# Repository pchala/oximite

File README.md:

# oximite

**oximite** is an asynchronous Rust firmware suite for the Pimoroni Pico Plus 2 W (RP2350B). It retrofits domestic espresso machines (such as the Gaggia Classic) with digital temperature control (with flow feed-forward), unified pressure/flow pump profiling, a lightweight offline web UI on port 80, and a native desktop companion application (`control/`) over TCP port 8080.

Special thanks to [Pimoroni](https://pimoroni.com) for providing hardware.

Support development by [leaving a tip on Ko-fi](https://ko-fi.com/J5E121FXSB).

## Workspace layout

- `proto/`: Shared `no_std` domain models and Port 80/8080 wire codecs (`oximite-proto`).
- `firmware/`: RP2350B firmware and lightweight offline HTML dashboard.
- `host-tests/`: Host unit, property/fuzz, and closed-loop simulation test suite.
- `control/`: Native Rust desktop application (`oximite-control`) for live graphing, PID tuning, profile editing, and bench sweeps.

## Getting started

- Repository layout, build, and test commands: [AGENTS.md](AGENTS.md).
- Documentation: [docs/](docs/). Start at [Requirements](docs/requirements.md).
- First-time setup: [Operations](docs/operations.md).

## Disclaimer

All hardware designs, code, and documentation are provided "AS IS", without warranty of any kind.
You are solely responsible for electrical and thermal safety when working with AC mains voltages and pressurized steam boilers.

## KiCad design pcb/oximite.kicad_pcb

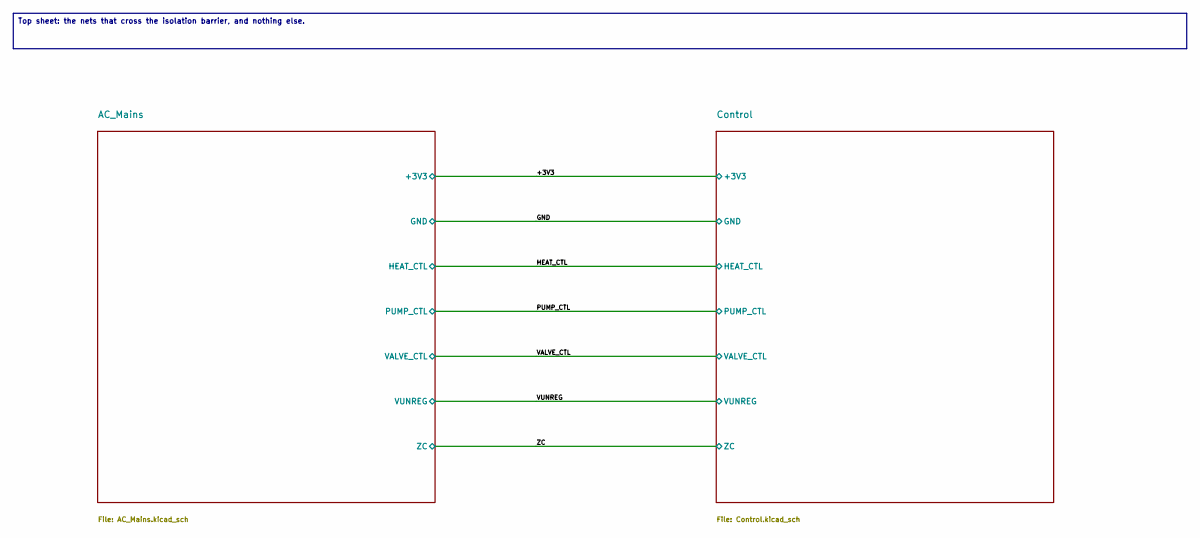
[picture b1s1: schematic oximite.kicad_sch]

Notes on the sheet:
Top sheet: the nets that cross the isolation barrier, and nothing else.

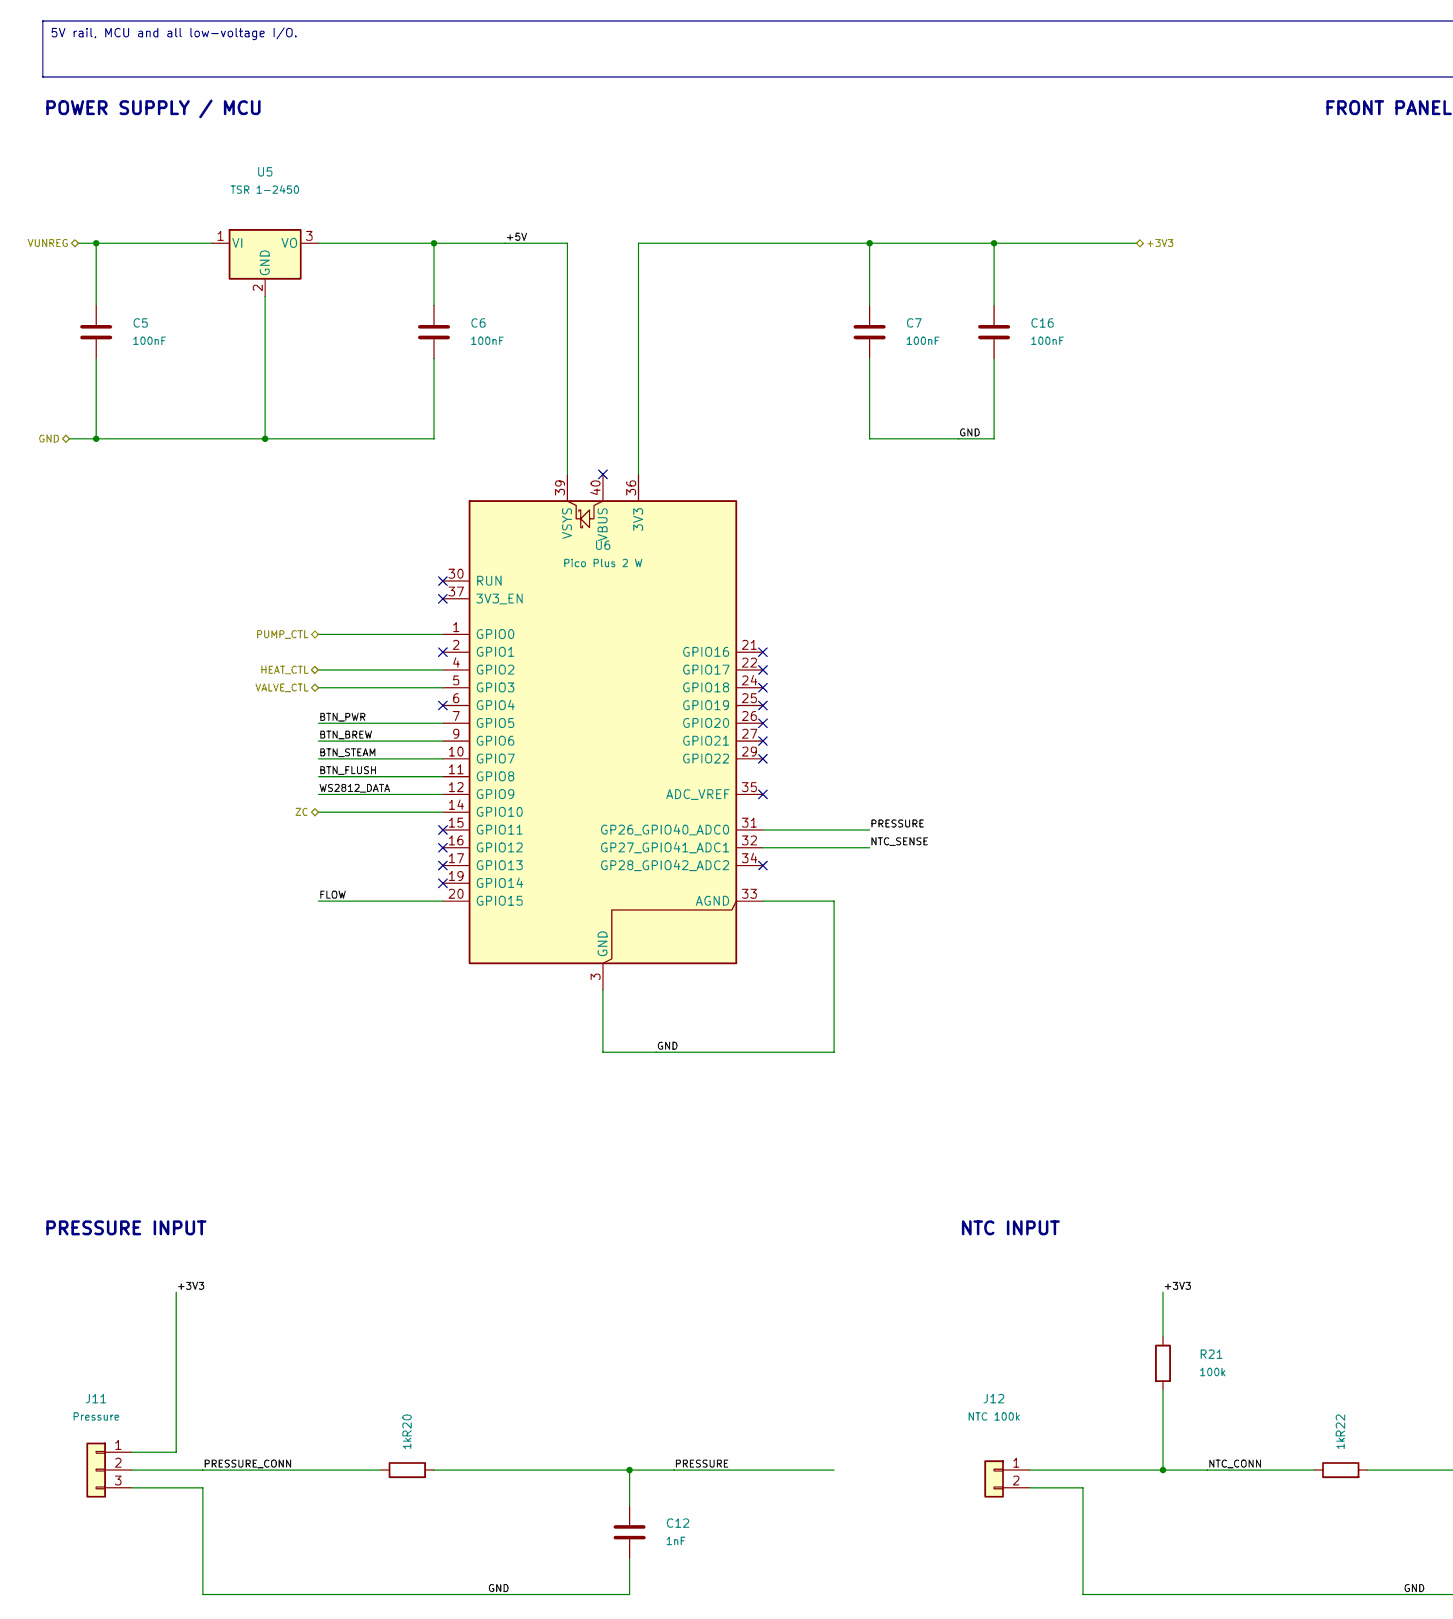
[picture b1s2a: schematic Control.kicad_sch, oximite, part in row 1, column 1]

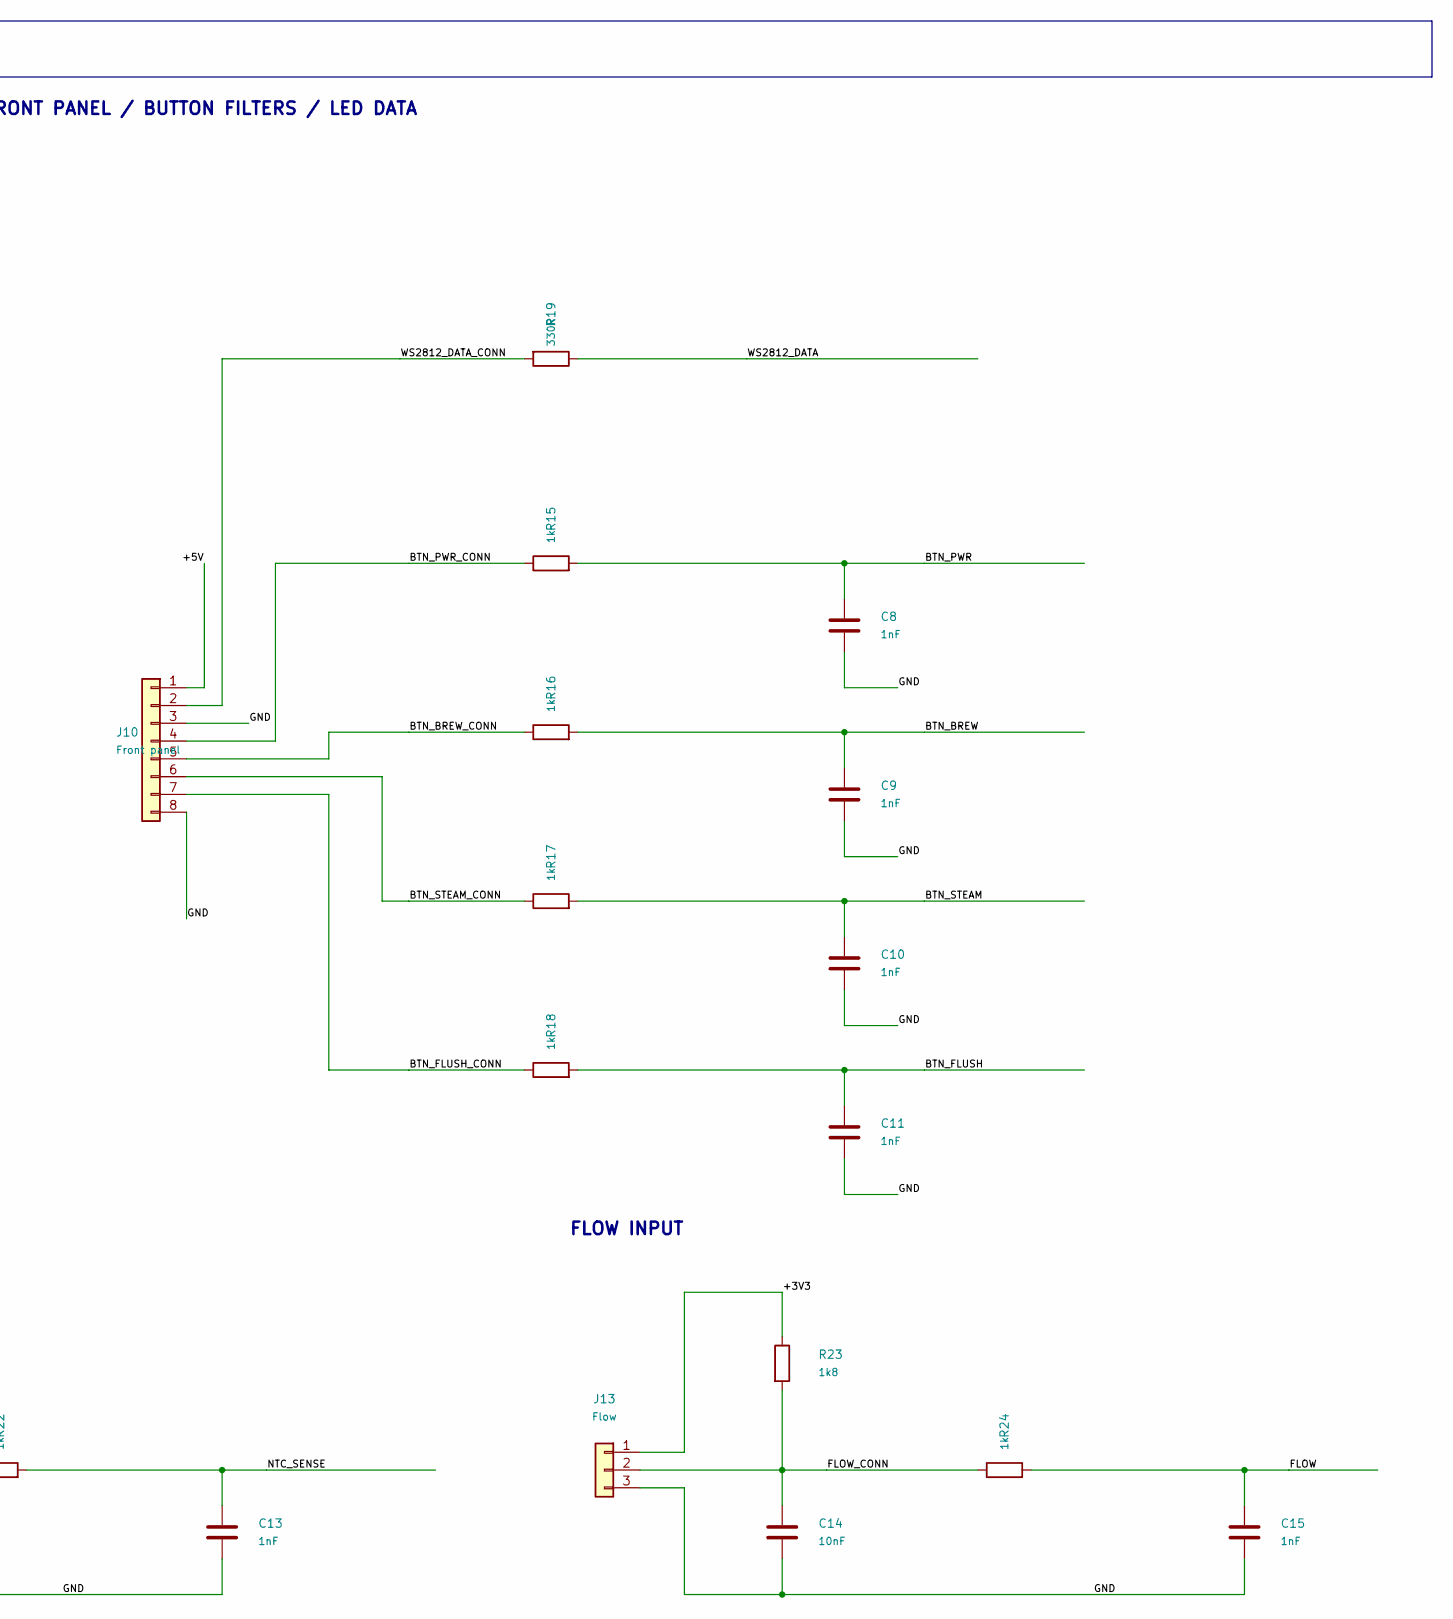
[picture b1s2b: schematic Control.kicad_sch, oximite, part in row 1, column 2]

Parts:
C5, C6, C7, C16: 100nF; C_0603_1608Metric
C8, C9, C10, C11, C12, C13, C15: 1nF; C_0603_1608Metric
C14: 10nF; C_0603_1608Metric
J10: Front panel; JST_XH_B8B-XH-A_1x08_P2.50mm_Vertical
J11: Pressure; JST_XH_B3B-XH-A_1x03_P2.50mm_Vertical
J12: NTC 100k; JST_XH_B2B-XH-A_1x02_P2.50mm_Vertical
J13: Flow; JST_XH_B3B-XH-A_1x03_P2.50mm_Vertical
R15, R16, R17, R18, R20, R22, R24: 1k; R_0603_1608Metric
R19: 330R; R_0603_1608Metric
R21: 100k; R_0603_1608Metric
R23: 1k8; R_0603_1608Metric
U5: TSR 1-2450; Converter_DCDC_TRACO_TSR-1_THT
U6: Pico Plus 2 W; Pimoroni_Pico_Plus_2_W_Header_Mount

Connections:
/+3V3: C7.1, C16.1, J11.1, J13.1, R21.1, R23.1, U6.36 (3V3); also elsewhere on the board
/Control/+5V: C6.1, J10.1, U5.3 (VO), U6.39 (VSYS)
/Control/BTN_BREW: C9.1, R16.2, U6.9 (GPIO6)
/Control/BTN_BREW_CONN: J10.5, R16.1
/Control/BTN_FLUSH: C11.1, R18.2, U6.11 (GPIO8)
/Control/BTN_FLUSH_CONN: J10.7, R18.1
/Control/BTN_PWR: C8.1, R15.2, U6.7 (GPIO5)
/Control/BTN_PWR_CONN: J10.4, R15.1
/Control/BTN_STEAM: C10.1, R17.2, U6.10 (GPIO7)
/Control/BTN_STEAM_CONN: J10.6, R17.1
/Control/FLOW: C15.1, R24.2, U6.20 (GPIO15)
/Control/FLOW_CONN: C14.1, J13.2, R23.2, R24.1
/Control/NTC_CONN: J12.1, R21.2, R22.1
/Control/NTC_SENSE: C13.1, R22.2, U6.32 (GP27_GPIO41_ADC1)
/Control/PRESSURE: C12.1, R20.2, U6.31 (GP26_GPIO40_ADC0)
/Control/PRESSURE_CONN: J11.2, R20.1
/Control/WS2812_DATA: R19.1, U6.12 (GPIO9)
/Control/WS2812_DATA_CONN: J10.2, R19.2
/GND: C5.2, C6.2, C7.2, C8.2, C9.2, C10.2, C11.2, C12.2, C13.2, C14.2, C15.2, C16.2, J10.3, J10.8, J11.3, J12.2, J13.3, U5.2 (GND), U6.3 (GND), U6.8 (GND), U6.13 (GND), U6.18 (GND), U6.23 (GND), U6.28 (GND), U6.33 (AGND), U6.38 (GND); also elsewhere on the board
/HEAT_CTL: U6.4 (GPIO2); also elsewhere on the board
/PUMP_CTL: U6.1 (GPIO0); also elsewhere on the board
/VALVE_CTL: U6.5 (GPIO3); also elsewhere on the board
/VUNREG: C5.1, U5.1 (VI); also elsewhere on the board
/ZC: U6.14 (GPIO10); also elsewhere on the board

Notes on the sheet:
5V rail, MCU and all low-voltage I/O.
POWER SUPPLY / MCU
FRONT PANEL / BUTTON FILTERS / LED DATA
PRESSURE INPUT
NTC INPUT
FLOW INPUT

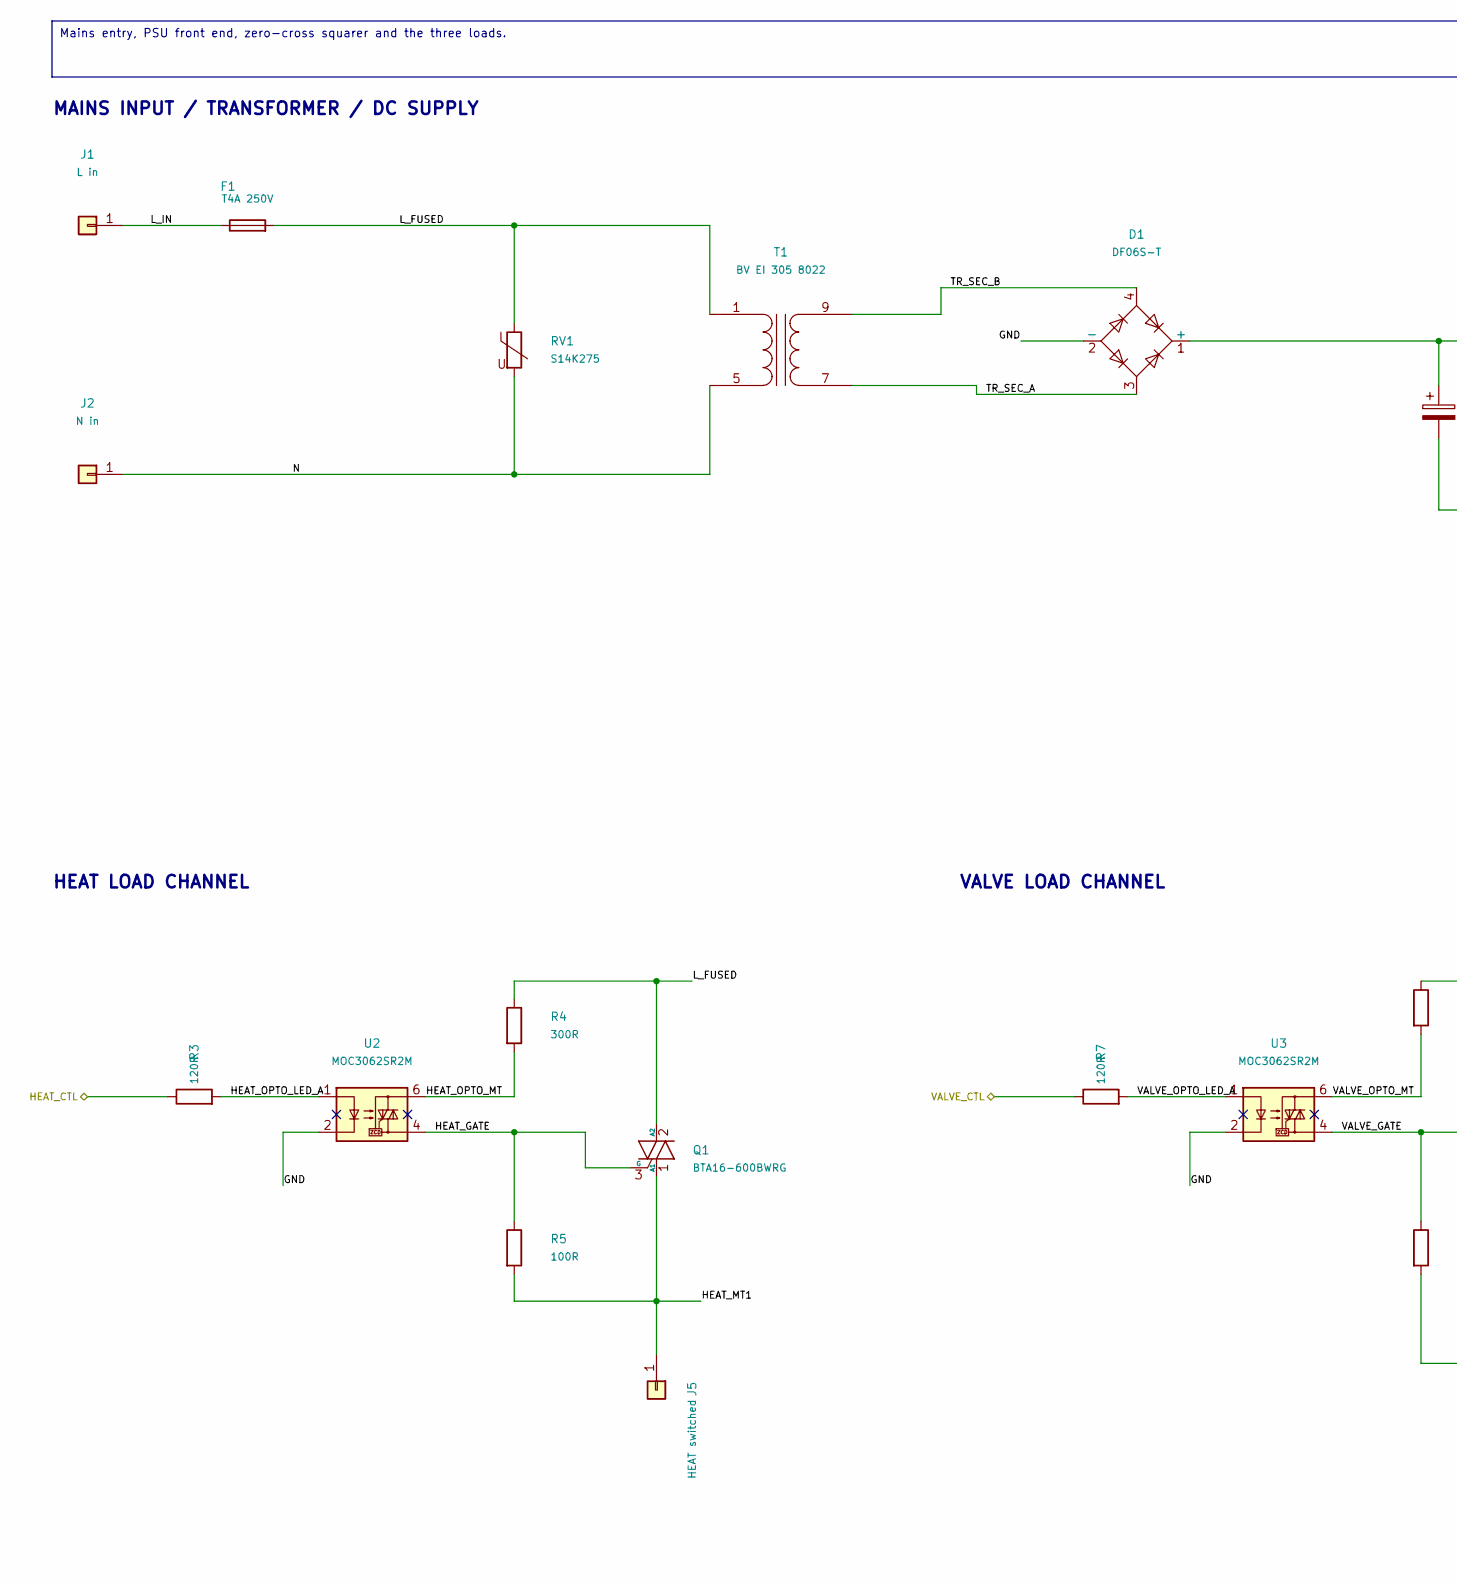
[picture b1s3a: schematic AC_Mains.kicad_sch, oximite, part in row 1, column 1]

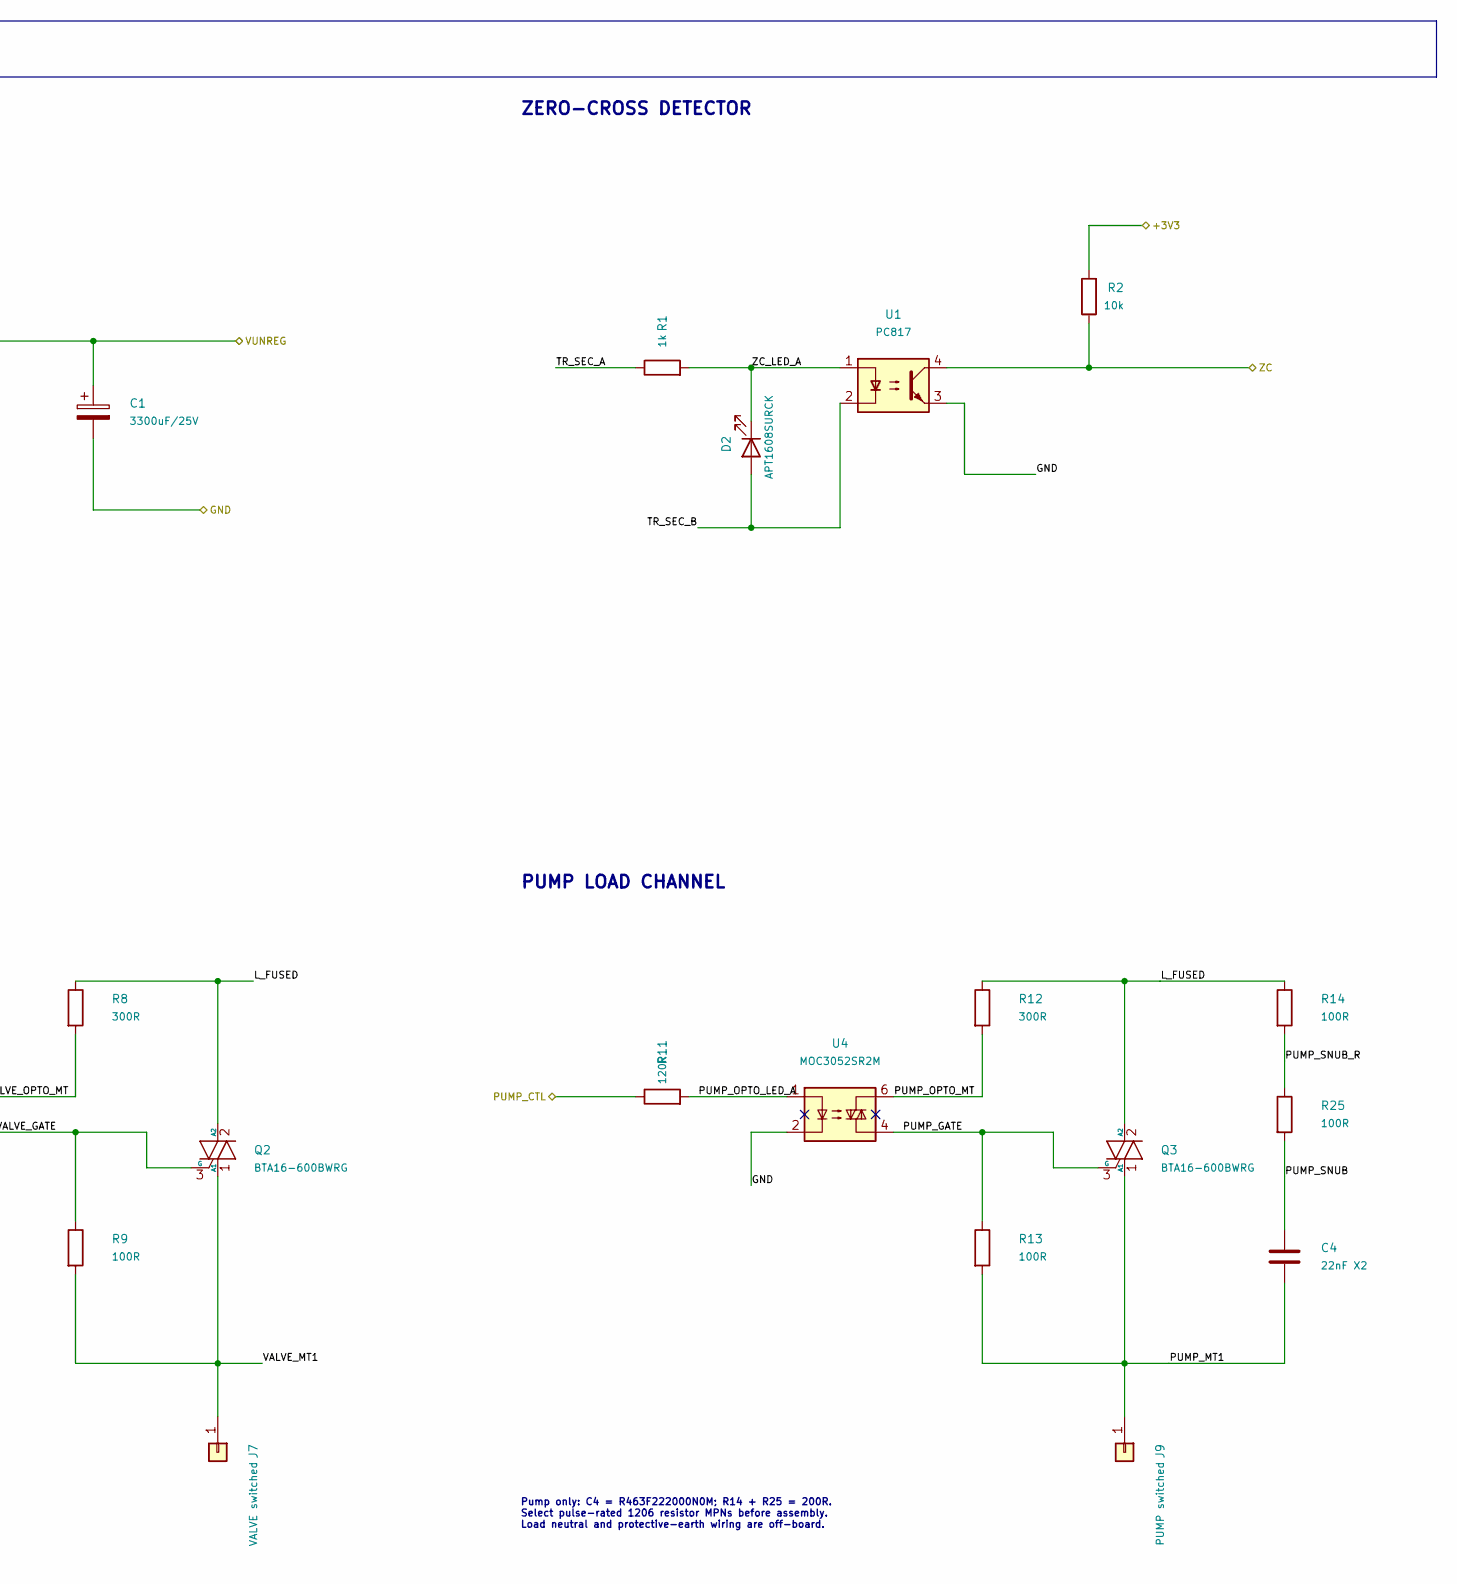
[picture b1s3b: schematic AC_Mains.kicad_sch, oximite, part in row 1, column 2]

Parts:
C1: 3300uF/25V; CP_Radial_D12.5mm_P5.00mm
C4: 22nF X2; C_Rect_L13.0mm_W4.0mm_P10.00mm_FKS3_FKP3_MKS4
D1: DF06S-T; Diode_Bridge_OnSemi_SDIP-4L
D2: APT1608SURCK; LED_0603_1608Metric
F1: T4A 250V; Fuseholder_Clip-5x20mm_Keystone_3517_Inline_P23.11x6.76mm_D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
J1: L in; Spade_6.35mm_Keystone_1287
J2: N in; Spade_6.35mm_Keystone_1287
J5: HEAT switched; Spade_6.35mm_Keystone_1287
J7: VALVE switched; Spade_6.35mm_Keystone_1287
J9: PUMP switched; Spade_6.35mm_Keystone_1287
Q1, Q2, Q3: BTA16-600BWRG; TO-220-3_Vertical
R1: 1k; R_1206_3216Metric
R2: 10k; R_0603_1608Metric
R3, R7, R11: 120R; R_0805_2012Metric
R4, R8, R12: 300R; R_1206_3216Metric
R5, R9, R13, R14, R25: 100R; R_1206_3216Metric
RV1: S14K275; RV_Disc_D16.5mm_W6.7mm_P7.5mm
T1: BV EI 305 8022; Transformer_Hahn_BV_EI_305
U1: PC817; SOP-4_4.4x2.6mm_P1.27mm
U2, U3: MOC3062SR2M; SMDIP-6_W9.53mm_Clearance8mm
U4: MOC3052SR2M; SMDIP-6_W9.53mm_Clearance8mm

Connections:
/+3V3: R2.2; also elsewhere on the board
/AC_Mains/HEAT_GATE: Q1.3 (G), R5.1, U2.4
/AC_Mains/HEAT_MT1: J5.1, Q1.1 (A1), R5.2
/AC_Mains/HEAT_OPTO_LED_A: R3.2, U2.1
/AC_Mains/HEAT_OPTO_MT: R4.2, U2.6
/AC_Mains/L_FUSED: F1.2, Q1.2 (A2), Q2.2 (A2), Q3.2 (A2), R4.1, R8.1, R12.1, R14.1, RV1.1, T1.1
/AC_Mains/L_IN: F1.1, J1.1
/AC_Mains/N: J2.1, RV1.2, T1.5 (P2)
/AC_Mains/PUMP_GATE: Q3.3 (G), R13.1, U4.4
/AC_Mains/PUMP_MT1: C4.2, J9.1, Q3.1 (A1), R13.2
/AC_Mains/PUMP_OPTO_LED_A: R11.2, U4.1
/AC_Mains/PUMP_OPTO_MT: R12.2, U4.6
/AC_Mains/PUMP_SNUB: C4.1, R25.2
/AC_Mains/PUMP_SNUB_R: R14.2, R25.1
/AC_Mains/TR_SEC_A: D1.3, R1.1, T1.7 (S1)
/AC_Mains/TR_SEC_B: D1.4, D2.2 (A), T1.9 (S2), U1.2
/AC_Mains/VALVE_GATE: Q2.3 (G), R9.1, U3.4
/AC_Mains/VALVE_MT1: J7.1, Q2.1 (A1), R9.2
/AC_Mains/VALVE_OPTO_LED_A: R7.2, U3.1
/AC_Mains/VALVE_OPTO_MT: R8.2, U3.6
/AC_Mains/ZC_LED_A: D2.1 (K), R1.2, U1.1
/GND: C1.2, D1.2 (-), U1.3, U2.2, U3.2, U4.2; also elsewhere on the board
/HEAT_CTL: R3.1; also elsewhere on the board
/PUMP_CTL: R11.1; also elsewhere on the board
/VALVE_CTL: R7.1; also elsewhere on the board
/VUNREG: C1.1, D1.1 (+); also elsewhere on the board
/ZC: R2.1, U1.4; also elsewhere on the board

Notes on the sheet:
VALVE LOAD CHANNEL
PUMP LOAD CHANNEL
HEAT LOAD CHANNEL
MAINS INPUT / TRANSFORMER / DC SUPPLY
ZERO-CROSS DETECTOR
Mains entry, PSU front end, zero-cross squarer and the three loads.
Pump only: C4 = R463F222000N0M; R14 + R25 = 200R. Select pulse-rated 1206 resistor MPNs before assembly. Load neutral and protective-earth wiring are off-board.

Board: 2 copper layers, 64 parts (1 on the bottom side), 44 nets, no tracks yet.

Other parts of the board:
H1, H2, H3, H4: M3 corner mounting; MountingHole_3.2mm_M3

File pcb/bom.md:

# Bill of Materials: Oximite

Source: `oximite.csv` (28 line items). Parts are merged by value and footprint.
Part numbers come from the JLCPCB parts API (`jlcpcb_mcp`), ranked Basic first, then price, in stock. Prices are USD per unit at qty 10 and were checked on 2026-10-29. Stock and library type can change, so confirm in the JLCPCB order flow.

**Lib**: B = Basic (no feeder fee), E = Extended.

## 1. Passives (all Basic)

| Value | Footprint | Qty | RefDes | LCSC | Lib | Stock | Price | MPN |
|---|---|---|---|---|---|---|---|---|
| 1k 1% | 0603 | 7 | R15, R16, R17, R18, R20, R22, R24 | `C21190` | B | 32.2M | 0.0017 | 0603WAF1001T5E |
| 1k 1% | 1206 | 1 | R1 | `C4410` | B | 1.78M | 0.0085 | 1206W4F1001T5E |
| 10k 1% | 0603 | 1 | R2 | `C25804` | B | 37.3M | 0.0022 | 0603WAF1002T5E |
| 100k 1% | 0603 | 1 | R21 | `C25803` | B | 18.1M | 0.0029 | 0603WAF1003T5E |
| 1k8 1% | 0603 | 1 | R23 | `C4177` | B | 677k | 0.0021 | 0603WAF1801T5E |
| 330R 1% | 0603 | 1 | R19 | `C23138` | B | 3.48M | 0.0020 | 0603WAF3300T5E |
| 120R 1% | 0805 | 3 | R3, R7, R11 | `C17437` | B | 1.25M | 0.0066 | 0805W8F1200T5E |
| 300R 1% | 1206 | 3 | R4, R8, R12 | `C17887` | B | 356k | 0.0048 | 1206W4F3000T5E |
| 100R 1% | 1206 | 5 | R5, R9, R13, R14, R25 | `C17901` | B | 2.40M | 0.0059 | 1206W4F1000T5E |
| 100nF 50V X7R | 0603 | 4 | C5, C6, C7, C16 | `C14663` | B | 38.7M | 0.0102 | CC0603KRX7R9BB104 |
| 1nF 50V X7R | 0603 | 7 | C8, C9, C10, C11, C12, C13, C15 | `C1588` | B | 5.18M | 0.0098 | CL10B102KB8NNNC |
| 10nF 50V X7R | 0603 | 1 | C14 | `C57112` | B | 5.76M | 0.0103 | 0603B103K500NT |
| Red LED (replaces APT1608SURCK) | 0603 | 1 | D2 | `C2286` | B | 7.36M | 0.0077 | KT-0603R |

The CSV LED is APT1608SURCK (`C5875723`, Extended, $0.126). `C2286` is a Basic red 0603 LED with similar specs (20 mA, 300 mcd) and is much cheaper. Check that the brightness suits your front panel.

## 2. Power and protection

| Part | Footprint | Qty | RefDes | LCSC | Lib | Stock | Price | Note |
|---|---|---|---|---|---|---|---|---|
| 3300uF 25V electrolytic | THT D13 mm, 5 mm pitch | 1 | C1 | `C45068` | E | 5.2k | 0.329 | KM338M025J25RR0VH2FP0, D13xL25, matches the 12.5 mm footprint |
| 22nF film capacitor, P=10 mm | THT | 1 | C4 | `C390074` | E | 21.6k | 0.048 | KP223J2J1001, 630V PP film. Not X2 rated, see notes |
| Varistor S14K275 equivalent (14D431K, 275V, P=7.5 mm) | THT D16.5 mm | 1 | RV1 | `C49069732` | E | 4.4k | 0.091 | 115J, 4.5kA |
| DF06S bridge rectifier | DFS | 1 | D1 | `C54444823` | E | 8.2k | 0.0245 | 1A, 600V. Alternative `C5255305` (28k stock, $0.050) |
| TSR 1-2450 (5V, 1A, SIP) | SIP 11.6x7.5 mm | 1 | U5 | `C53183920` | E | 1.2k | 4.75 | Pin compatible 5V 1A, 7V to 36V in. Cheaper `C54450743` ($3.49, 346 stock) unverified |
| T4A 250V fuse holder, 5x20 mm clip | Keystone 3517 | 1 | F1 | not found | | | | Buy from LCSC or Mouser manually |
| Transformer Hahn BV EI 305 8022 | custom | 1 | T1 | not found | | | | Not a JLCPCB part, order from Hahn |
| Resettable fuse 60 mA hold, 250 V (new, in series with T1 primary) | THT P=5.1 mm | 1 | new | `C369126` | E | 21.7k | 0.048 | JK250-060U. Protects the small transformer only. Not in the CSV, needs a schematic and footprint |

## 3. Switching and isolation

| Part | Footprint | Qty | RefDes | LCSC | Lib | Stock | Price | Note |
|---|---|---|---|---|---|---|---|---|
| BTA16-600BWRG triac | TO-220 | 3 | Q1, Q2, Q3 | `C7469136` | E | 163 | 0.336 | 600V 16A, exact RG variant. Low stock. Alternative `C7471859` (990 stock, $0.328) |
| MOC3062S optotriac | SMDIP-6 | 2 | U2, U3 | `C22373369` | E | 293 | 0.322 | MOC3062SM. Alternative `C22469446` (935 stock, $0.266, UMW) |
| MOC3052S optotriac | SMDIP-6 | 1 | U4 | `C3014301` | E | 30.2k | 0.214 | MOC3052SM(UMW), well stocked |
| PC817 optocoupler | SOP-4 | 1 | U1 | `C20612591` | E | 128k | 0.0385 | PC817CS. Alternative `C17701950` ($0.034) |

## 4. Controller

| Part | Footprint | Qty | RefDes | Note |
|---|---|---|---|---|
| Pimoroni Pico Plus 2 W | Header mount | 1 | U6 | Not a JLCPCB part, order from [Pimoroni](https://shop.pimoroni.com/products/pimoroni-pico-plus-2-w) |

## 5. Connectors

| Part | Footprint | Qty | RefDes | LCSC | Lib | Stock | Price |
|---|---|---|---|---|---|---|---|
| JST XH 8-pin B8B-XH-A | THT 2.5 mm | 1 | J10 | `C157972` | E | 16.5k | 0.142 |
| JST XH 3-pin B3B-XH-A | THT 2.5 mm | 2 | J11, J13 | `C144394` | E | 70.2k | 0.0546 |
| JST XH 2-pin B2B-XH-A | THT 2.5 mm | 1 | J12 | `C158012` | E | 641k | 0.0408 |
| Spade 6.35 mm (Keystone 1287) | custom | 5 | J1, J2, J5, J7, J9 | `C238078` | E | 2.3k | 0.136 |

Cheaper generic 6.3 mm PCB quick terminals exist (BZXC, e.g. `C20626100` at $0.035, 4.2k stock, `C20626104` at $0.037, 13k stock). Their pin and tab geometry differs from the Keystone 1287, so the custom `oximite` footprint would need checking.

The JST part numbers above are genuine JST B*B-XH-A parts. Cheaper clones exist (`C10385` for 8-pin at $0.028, `C51940188` for 3-pin at $0.012, `C51940134` for 2-pin at $0.010) if you accept non-JST.

## 6. Notes

- All 13 passive lines are Basic, so they add no extended-part fees.
- Everything else is Extended. That is 12 extended lines, so expect a per-part feeder fee on each (roughly $3 each at JLCPCB).
- Not found on JLCPCB: fuse holder, Hahn transformer and Pico Plus 2 W. Source these elsewhere, for example Mouser, DigiKey or Pimoroni.
- C4 is marked X2 in the CSV (mains across-the-line capacitor). `C390074` is a 630V film part but not X2 certified. For safety use a proper X2 part such as an Epcos B32922 or Kemet R46 and buy it elsewhere.
- BTA16-600BWRG stock on JLCPCB is low (163), so check availability for your build quantity.
- The varistor and DC/DC choices are electrical equivalents, not identical to the original MPNs. Verify the datasheets before ordering.

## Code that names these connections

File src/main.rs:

#![no_std]
#![no_main]

mod adc;
mod board;
mod buttons;
mod control;
mod coordinator;
mod cyw43_nvram;
mod dhcp;
mod flow_meter;
mod leds;
mod operations;
mod pid;
mod profiles;
mod settings;
mod state;
mod web_api;
mod wifi_task;

use embassy_executor::Spawner;
use embassy_rp::adc::{Adc, Config as AdcConfig};
use embassy_rp::bind_interrupts;
use embassy_rp::flash::Flash;
use embassy_rp::gpio::{Input, Level, Output, Pull};
use embassy_rp::multicore::{spawn_core1, Stack as CoreStack};
use embassy_rp::peripherals::{DMA_CH0, DMA_CH1, PIO0, PIO1, PIO2};
use static_cell::{ConstStaticCell, StaticCell};
use {defmt_rtt as _, panic_probe as _};

use crate::settings::SettingsStore;

static CORE1_STACK: ConstStaticCell<CoreStack<32768>> = ConstStaticCell::new(CoreStack::new());
static EXECUTOR_CORE1: StaticCell<embassy_executor::Executor> = StaticCell::new();

bind_interrupts!(pub struct Irqs {
    PIO0_IRQ_0 => embassy_rp::pio::InterruptHandler<PIO0>;
    PIO1_IRQ_0 => embassy_rp::pio::InterruptHandler<PIO1>;
    PIO2_IRQ_0 => embassy_rp::pio::InterruptHandler<PIO2>;
    ADC_IRQ_FIFO => embassy_rp::adc::InterruptHandler;
    // Every DMA channel shares DMA_IRQ_0, so both handlers bind to the same line.
    // CH0 = cyw43 SPI (serviced on core1), CH1 = flash.
    DMA_IRQ_0 => embassy_rp::dma::InterruptHandler<DMA_CH0>, embassy_rp::dma::InterruptHandler<DMA_CH1>;
});

// ==========================================
// MAIN
// ==========================================
#[embassy_executor::main]
async fn main(spawner: Spawner) {
    let p = embassy_rp::init(Default::default());

    // Initialize unused pins to Output Low to improve EMI immunity and power efficiency.
    // Safe-boot fallback: if the 'flush' button (PIN 8) is held during boot, force AP mode.
    let force_ap = unsafe {
        let p_steal = embassy_rp::Peripherals::steal();
        macro_rules! init_pins_low {
            ($p:expr; $($pin:ident),*) => {
                $(let _ = Output::new($p.$pin, Level::Low);)*
            };
        }
        init_pins_low!(p_steal; PIN_1, PIN_4, PIN_11, PIN_12, PIN_13, PIN_14, PIN_16, PIN_17, PIN_18, PIN_19, PIN_20, PIN_21, PIN_22, PIN_28);
        // GP26-27 share the A0-A1 analog nets — keep as HiZ so they don't load the ADC inputs
        macro_rules! init_pins_hiz {
            ($p:expr; $($pin:ident),*) => {
                $(let _ = Input::new($p.$pin, Pull::None);)*
            };
        }
        init_pins_hiz!(p_steal; PIN_26, PIN_27);

        Input::new(p_steal.PIN_8, Pull::Up).is_low()
    };
    if force_ap {
        defmt::warn!("Hardware override: Forcing AP mode!");
    }

    let mut flash: Flash<'static, _, embassy_rp::flash::Async, { board::FLASH_SIZE }> =
        Flash::new(p.FLASH, p.DMA_CH1, Irqs);
    SettingsStore::load(&mut flash).await;
    crate::profiles::load_all_profiles_from_flash(&mut flash).await;

    let embassy_rp::pio::Pio {
        common: mut common1,
        sm0: sm1_0,
        irq0: irq1_0,
        ..
    } = embassy_rp::pio::Pio::new(p.PIO1, Irqs);

    let (pwr, spi) = {
        let pwr = Output::new(p.PIN_23, Level::Low);
        let cs = Output::new(p.PIN_25, Level::High);
        let spi = cyw43_pio::PioSpi::new(
            &mut common1,
            sm1_0,
            cyw43_pio::DEFAULT_CLOCK_DIVIDER,
            irq1_0,
            cs,
            p.PIN_24,
            p.PIN_29,
            embassy_rp::dma::Channel::new(p.DMA_CH0, Irqs),
        );
        (pwr, spi)
    };

    let vtor = unsafe { (*cortex_m::peripheral::SCB::PTR).vtor.read() };

    // Move PIO1_IRQ_0 and DMA_IRQ_0 from core0 to core1, so that servicing the
    // cyw43 SPI transfers never interrupts the zero-cross-synced triac/heater
    // timing on core0. Waking across cores is fine: the thread-mode pender is
    // `sev`, which is broadcast to both cores.
    //
    // ORDER MATTERS: the NVIC is per-core and these lines are enabled by
    // `Pio::new` / `dma::Channel::new`, which run on core0. Every such call
    // must stay ABOVE this point — constructing one below would re-enable the
    // interrupt on core0 and silently undo the reroute. That means `Flash::new`
    // and `PioSpi::new` above.
    //
    // Note the mask covers the whole line, not one channel: DMA_CH1 (flash) is
    // rerouted too, so `settings::flash_update_task` (core0) relies on core1
    // servicing its completions. embassy-rp hardwires every channel to
    // DMA_IRQ_0/`inte(0)`, so the two cannot be split onto separate lines.
    cortex_m::peripheral::NVIC::mask(embassy_rp::interrupt::Interrupt::PIO1_IRQ_0);
    cortex_m::peripheral::NVIC::mask(embassy_rp::interrupt::Interrupt::DMA_IRQ_0);

    defmt::info!("Spawning Core 1...");
    spawn_core1(p.CORE1, CORE1_STACK.take(), move || {
        unsafe {
            (*cortex_m::peripheral::SCB::PTR).vtor.write(vtor);
            cortex_m::asm::dsb();
            cortex_m::asm::isb();
            cortex_m::peripheral::NVIC::unmask(embassy_rp::interrupt::Interrupt::PIO1_IRQ_0);
            cortex_m::peripheral::NVIC::unmask(embassy_rp::interrupt::Interrupt::DMA_IRQ_0);
        }
        defmt::info!("Core 1: Starting...");

        let executor = EXECUTOR_CORE1.init(embassy_executor::Executor::new());
        executor.run(|spawner| {
            defmt::info!("Core 1: Spawning wifi_init_task");
            spawner.spawn(wifi_task::wifi_init_task(spawner, pwr, spi, force_ap).unwrap());
        })
    });

    let embassy_rp::pio::Pio {
        common: mut common0,
        mut sm0,
        mut sm1,
        mut sm2,
        ..
    } = embassy_rp::pio::Pio::new(p.PIO0, Irqs);

    let embassy_rp::pio::Pio {
        common: mut common2,
        sm0: mut sm2_0,
        sm1: mut sm2_1,
        ..
    } = embassy_rp::pio::Pio::new(p.PIO2, Irqs);

    let adc = Adc::new(p.ADC, Irqs, AdcConfig::default());

    // Flow meter and WS2812 LEDs both live on PIO2 (unrelated to the
    // zero-cross-synced group below), freeing two PIO0 SM slots for the
    // heater's PIO-driven pin control and keeping PIO0 exactly at its
    // 32-word instruction-memory budget (trigger + triac + heater = 25/32).
    let mut flow_pin = common2.make_pio_pin(p.PIN_15);
    flow_pin.set_pull(Pull::Up); // flow sensor requires a pull-up
    flow_meter::setup_flow_sm(&mut common2, &mut sm2_0, flow_pin);
    spawner.spawn(flow_meter::run_flow_task(sm2_0).unwrap());

    let zc_pin = common0.make_pio_pin(p.PIN_10);
    let triac_pin = common0.make_pio_pin(p.PIN_0);
    control::setup_trigger_sm(&mut common0, &mut sm1, &zc_pin);
    control::setup_triac_sm(&mut common0, &mut sm2, &triac_pin, &zc_pin);

    let heater_pin = common0.make_pio_pin(p.PIN_2);
    control::setup_heater_sm(&mut common0, &mut sm0, &heater_pin, &zc_pin);

    let led_pin = common2.make_pio_pin(p.PIN_9);
    leds::setup_ws2812_sm(&mut common2, &mut sm2_1, led_pin);
    spawner.spawn(leds::led_task(sm2_1).unwrap());

    // The PIO peripherals stay configured for the whole program, but `main`
    // returns once everything is spawned, which would drop these `Common`
    // handles. embassy-rp refcounts them and, on the last drop, resets every
    // registered PIO pin's FUNCSEL back to NULL — silently disconnecting GP0
    // (triac), GP2 (heater), GP9 (LEDs), GP10 (zero-cross) and GP15 (flow).
    // Worse, embassy-rp keeps that refcount in a single `static` shared by
    // PIO0/PIO1/PIO2 — a function-local static inside a default trait method is
    // one item, not one per impl — so the three blocks corrupt each other's
    // counts and the wipe triggers here. Leak the handles:
    // they are owned for the lifetime of the firmware by design.
    core::mem::forget(common0);
    core::mem::forget(common1);
    core::mem::forget(common2);

    // A0 (GP40) = pressure sensor, A1 (GP41) = temperature sensor.
    // GP26-28 are already held HiZ above — they share the same PCB nets as A0-A2.
    let ch_press = embassy_rp::adc::Channel::new_pin(p.PIN_40, Pull::None);
    let ch_temp = embassy_rp::adc::Channel::new_pin(p.PIN_41, Pull::None);
    let valve_output = Output::new(p.PIN_3, Level::Low);

    spawner.spawn(adc::adc_task(adc, ch_press, ch_temp).unwrap());

    spawner.spawn(control::ac_sync_control_task(sm1, sm2, sm0).unwrap());

    let btn_power = Input::new(p.PIN_5, Pull::Up);
    let btn_brew = Input::new(p.PIN_6, Pull::Up);
    let btn_steam = Input::new(p.PIN_7, Pull::Up);
    let btn_flush = Input::new(p.PIN_8, Pull::Up);
    spawner.spawn(buttons::run_button_task(btn_power, btn_brew, btn_steam, btn_flush).unwrap());

    spawner.spawn(settings::flash_update_task(flash).unwrap());
    spawner.spawn(coordinator::coordinator_task(valve_output).unwrap());
}

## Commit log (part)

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2026-03-24 release 2
2026-06-22 cleanup
2026-06-23 some fixes
2026-06-26 flow control cleanup
2026-06-27 cleanup wifi
2026-06-27 cleanup html
2026-06-27 wifi simplification - flash update rename
2026-06-29 fix valve in Descale
2026-06-29 some cleanup
2026-06-29 align on pump power
2026-06-29 make proper descaling
2026-06-29 try to move irq to core1
2026-06-30 port to pico2
2026-06-30 fix(wifi): Wait for link to become up before monitoring for disconnections
2026-06-30 Revert "try to move irq to core1"
    This reverts commit eb24547670758d0c11ab4984887a8a5b8ace19c0.
2026-06-30 core1 workaround
